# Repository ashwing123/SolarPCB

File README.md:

# SolarPCB
Created a Printed Circuit Board (PCB) that harvests energy from a solar cell, with the main component being a bq25504 microcontroller that controls the overvoltage and undervoltage for effective charge storage in a 1F supercapacitor. Designed the schematic, layout, and created custom footprints for supercapacitor, switches, and other components.

Schematic:

Layout:

Working PCB:

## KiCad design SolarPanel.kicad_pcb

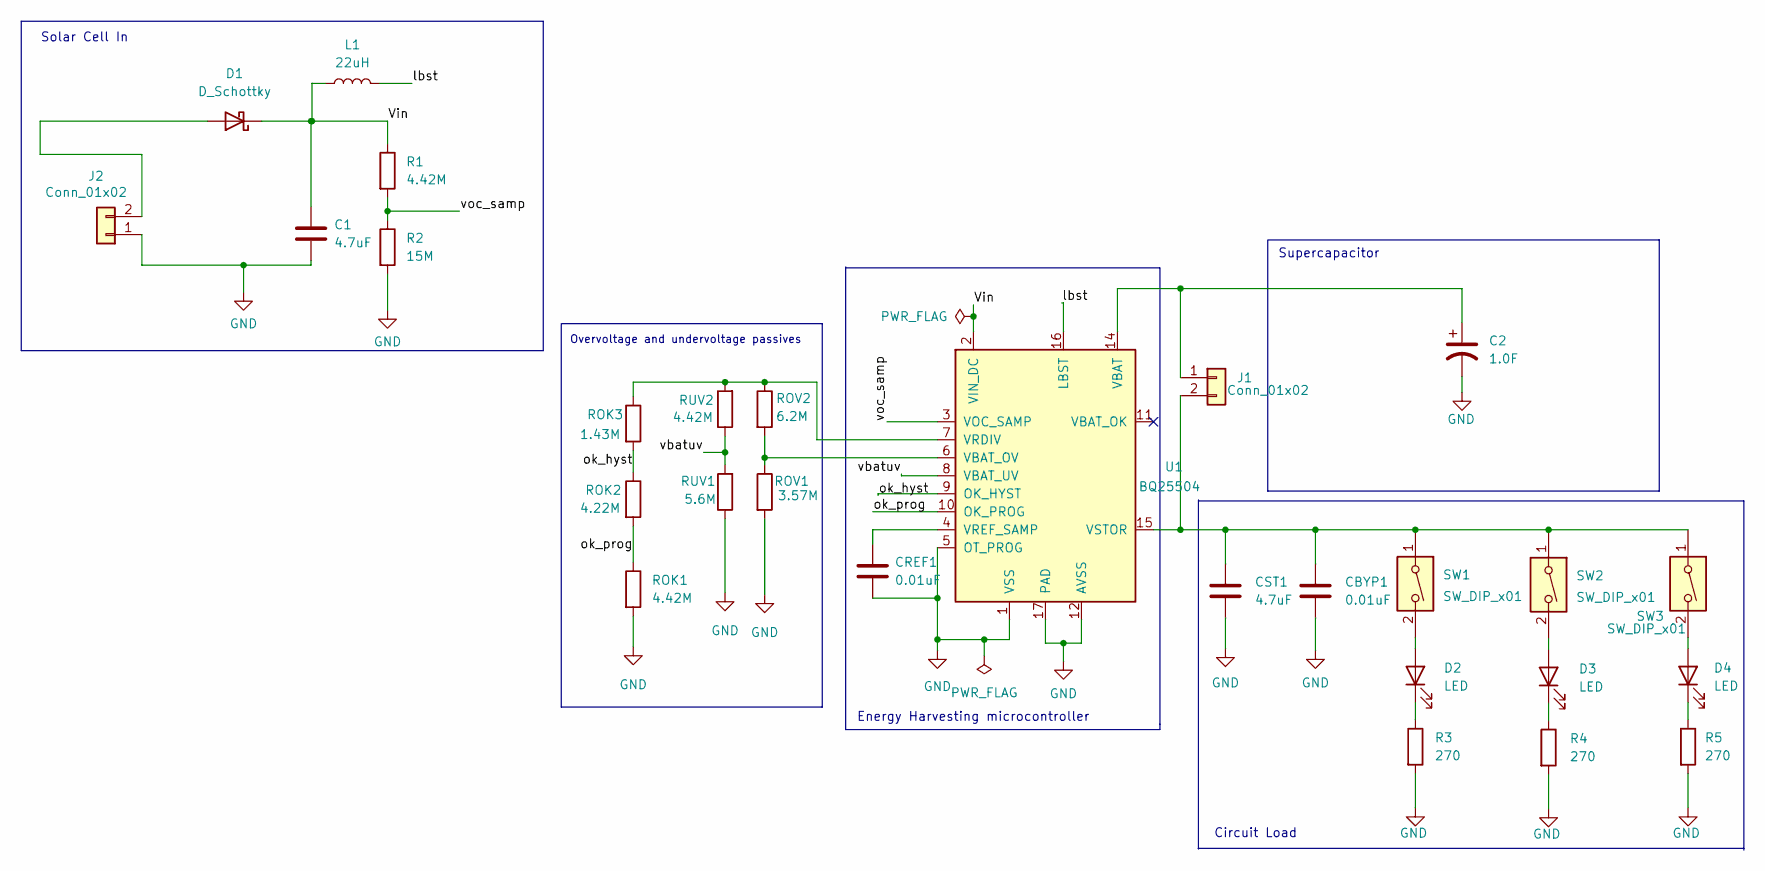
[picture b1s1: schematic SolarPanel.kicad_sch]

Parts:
C1: 4.7uF; C_0402_1005Metric
C2: 1.0F; SCAP
CBYP1: 0.01uF; C_0805_2012Metric
CREF1: 0.01uF; C_0805_2012Metric
CST1: 4.7uF; C_0402_1005Metric
D1: D_Schottky; D_SOD-123
D2, D3, D4: LED; LED_D5.0mm_Clear
J1, J2: Conn_01x02; PinHeader_1x02_P2.54mm_Vertical
L1: 22uH; L_1812_4532Metric
R1: 4.42M; R_1206_3216Metric
R2: 15M; R_1206_3216Metric
R3, R4, R5: 270; R_0402_1005Metric
ROK1: 4.42M; R_1206_3216Metric
ROK2: 4.22M; R_0805_2012Metric
ROK3: 1.43M; R_0603_1608Metric
ROV1: 3.57M; R_0805_2012Metric
ROV2: 6.2M; R_0603_1608Metric
RUV1: 5.6M; R_0603_1608Metric
RUV2: 4.42M; R_1206_3216Metric
SW1, SW2, SW3: SW_DIP_x01; Switch1
U1: BQ25504; QFN-16-1EP_3x3mm_P0.5mm_EP1.9x1.9mm

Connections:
/Vin: C1.1, D1.1 (K), L1.1, R1.1, U1.2 (VIN_DC)
/lbst: L1.2, U1.16 (LBST)
/ok_hyst: ROK2.1, ROK3.2, U1.9 (OK_HYST)
/ok_prog: ROK1.1, ROK2.2, U1.10 (OK_PROG)
/vbatuv: RUV1.2, RUV2.1, U1.8 (VBAT_UV)
/voc_samp: R1.2, R2.1, U1.3 (VOC_SAMP)
GND: C1.2, C2.2, CBYP1.2, CREF1.2, CST1.2, J2.1, R2.2, R3.2, R4.2, R5.2, ROK1.2, ROV1.2, RUV1.1, U1.1 (VSS), U1.5 (OT_PROG), U1.12 (AVSS), U1.13 (VSS), U1.17 (PAD)
unnamed: C2.1, J1.1, U1.14 (VBAT)
unnamed: CBYP1.1, CST1.1, J1.2, SW1.1, SW2.1, SW3.1, U1.15 (VSTOR)
unnamed: CREF1.1, U1.4 (VREF_SAMP)
unnamed: D1.2 (A), J2.2
unnamed: D2.1 (K), R3.1
unnamed: D2.2 (A), SW1.2
unnamed: D3.1 (K), R4.1
unnamed: D3.2 (A), SW2.2
unnamed: D4.1 (K), R5.1
unnamed: D4.2 (A), SW3.2
unnamed: ROK3.1, ROV2.1, RUV2.2, U1.7 (VRDIV)
unnamed: ROV1.1, ROV2.2, U1.6 (VBAT_OV)

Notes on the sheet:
Solar Cell In
Overvoltage and undervoltage passives
Energy Harvesting microcontroller
Circuit Load
Supercapacitor

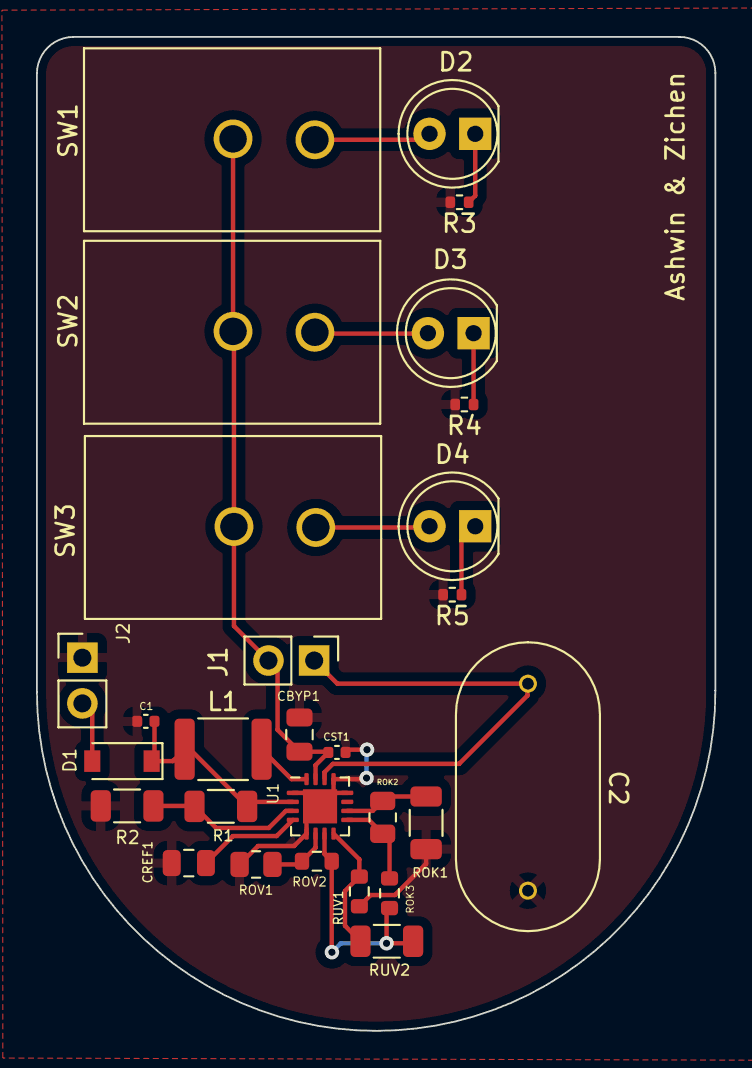
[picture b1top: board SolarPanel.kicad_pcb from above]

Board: 2 copper layers, 37.7 x 55.2 mm, 28 parts (0 on the bottom side), 19 nets.

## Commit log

2021-12-07 Added footprint and schematic
2021-12-07 project files
2021-12-07 Updated Readme to include pictures
2021-12-07 README updated with formatting
